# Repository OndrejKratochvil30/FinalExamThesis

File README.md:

# FinalExamThesis
FinalExamThesis

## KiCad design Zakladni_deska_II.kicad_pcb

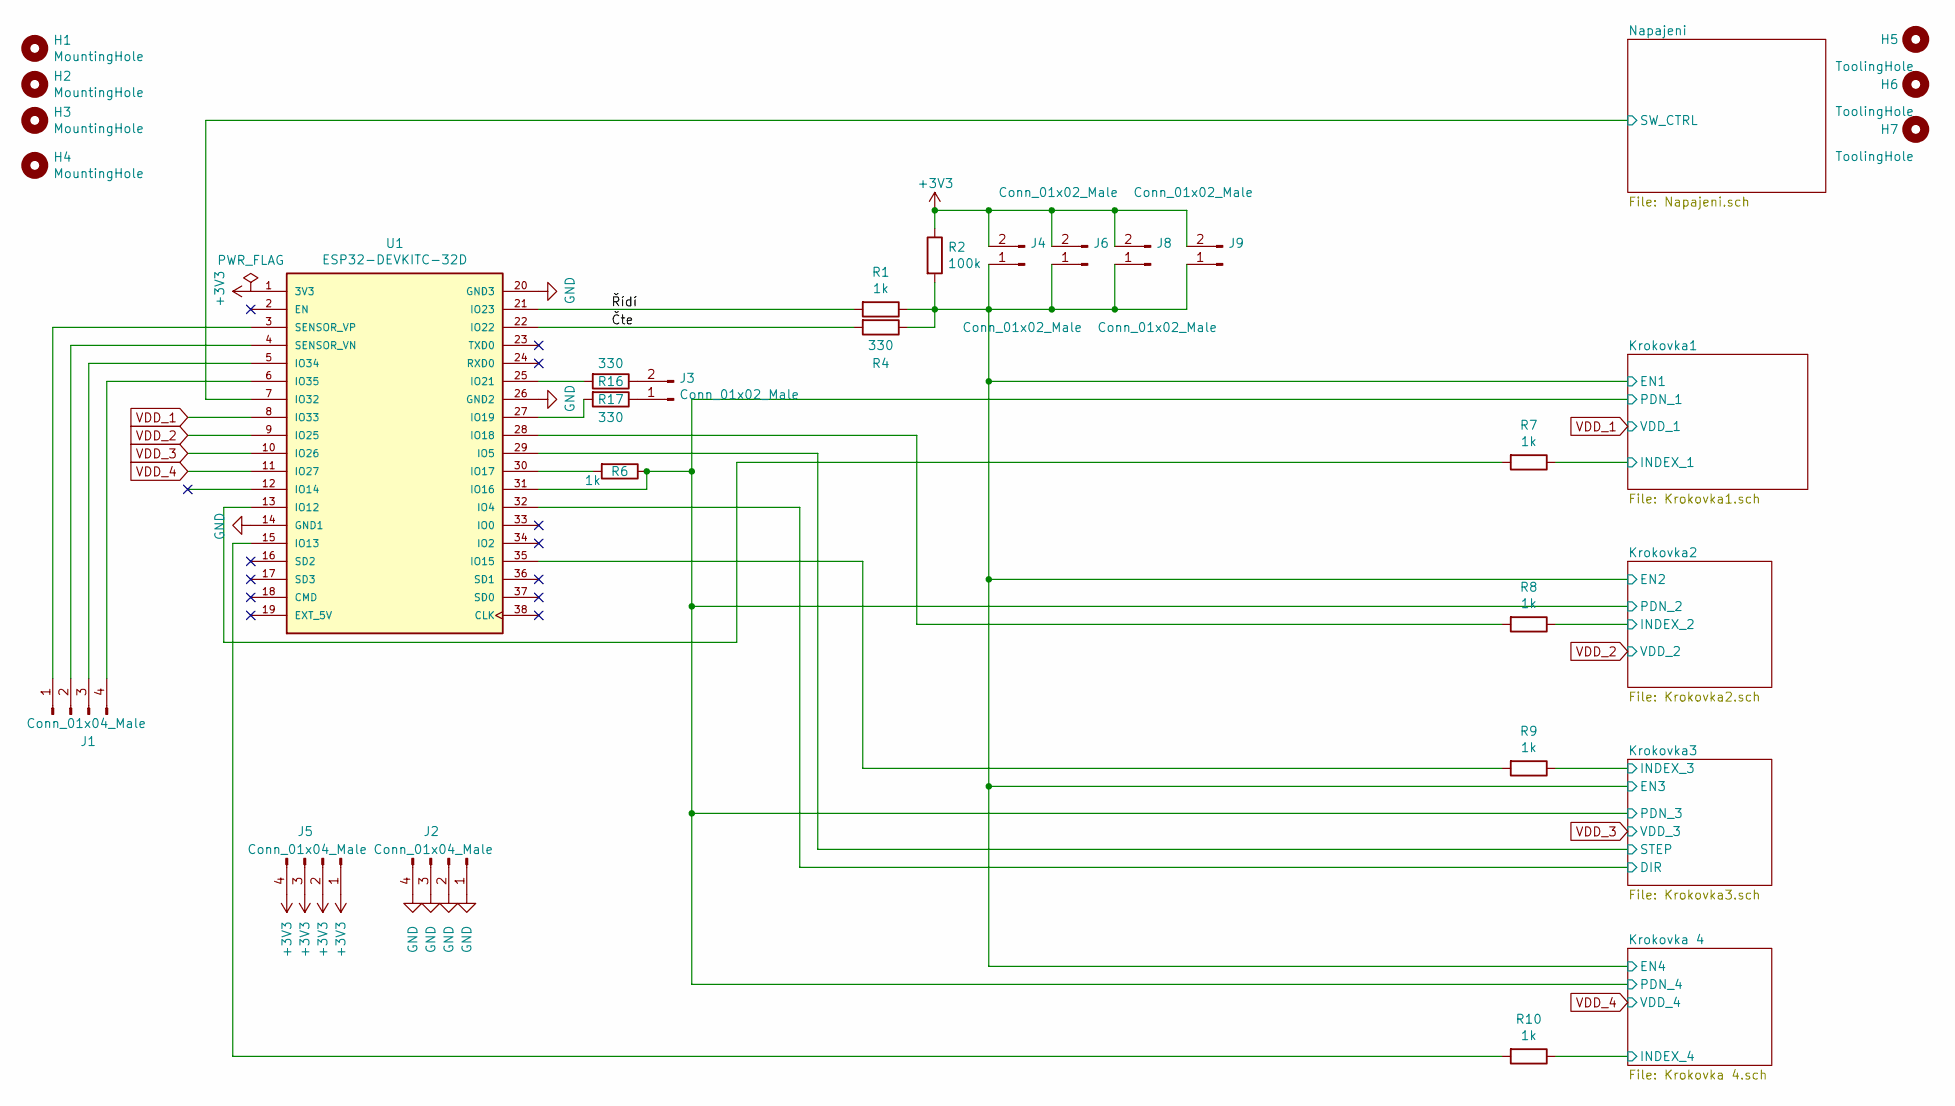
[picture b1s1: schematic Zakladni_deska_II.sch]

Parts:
H1, H2, H3, H4: MountingHole; MountingHole_2mm; JLCPCB_IGNORE 1
H5, H6, H7: ToolingHole; Tooling_Hole_2; JLCPCB_IGNORE 1
J1, J2, J5: Conn_01x04_Male; PinHeader_1x04_P2.54mm_Vertical; JLCPCB_IGNORE 1
J3, J4, J6, J8, J9: Conn_01x02_Male; PinHeader_1x02_P2.54mm_Vertical; JLCPCB_IGNORE 1
R1, R6, R7, R8, R9, R10: 1k; R_0805_2012Metric_Pad1.20x1.40mm_HandSolder; LCSC C17379
R2: 100k; R_0805_2012Metric_Pad1.20x1.40mm_HandSolder; LCSC C17422
R4, R16, R17: 330; R_0805_2012Metric_Pad1.20x1.40mm_HandSolder; LCSC C17617
U1: ESP32-DEVKITC-32D; MODULE_ESP32-DEVKITC-32D; PARTREV 4; JLCPCB_IGNORE 1

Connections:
+3V3: J4.2, J5.1, J5.2, J5.3, J5.4, J6.2, J8.2, J9.2, R2.1, U1.1 (3V3); also elsewhere on the board
/Krokovka1/EN1: J4.1, J6.1, J8.1, J9.1, R1.1, R2.2, R4.1; also elsewhere on the board
/Krokovka1/INDEX_1: R7.1; also elsewhere on the board
/Krokovka1/PDN_1: R6.1, U1.31 (IO16); also elsewhere on the board
/Krokovka2/INDEX_2: R8.1; also elsewhere on the board
/Krokovka3/DIR: U1.32 (IO4); also elsewhere on the board
/Krokovka3/INDEX_3: R9.1; also elsewhere on the board
/Krokovka3/STEP: U1.29 (IO5); also elsewhere on the board
/Krokovka 4/INDEX_4: R10.1; also elsewhere on the board
/Napajeni/SW_CTRL: U1.7 (IO32); also elsewhere on the board
/Čte: R4.2, U1.22 (IO22)
/Řídí: R1.2, U1.21 (IO23)
GND: J2.1, J2.2, J2.3, J2.4, U1.14 (GND1), U1.20 (GND3), U1.26 (GND2); also elsewhere on the board
unnamed: J1.1, U1.3 (SENSOR_VP)
unnamed: J1.2, U1.4 (SENSOR_VN)
unnamed: J1.3, U1.5 (IO34)
unnamed: J1.4, U1.6 (IO35)
unnamed: J3.1, R17.1
unnamed: J3.2, R16.1
unnamed: R6.2, U1.30 (IO17)
unnamed: R7.2, U1.13 (IO12)
unnamed: R8.2, U1.28 (IO18)
unnamed: R9.2, U1.35 (IO15)
unnamed: R10.2, U1.15 (IO13)
unnamed: R16.2, U1.25 (IO21)
unnamed: R17.2, U1.27 (IO19)
VDD_1: U1.8 (IO33); also elsewhere on the board
VDD_2: U1.9 (IO25); also elsewhere on the board
VDD_3: U1.10 (IO26); also elsewhere on the board
VDD_4: U1.11 (IO27); also elsewhere on the board

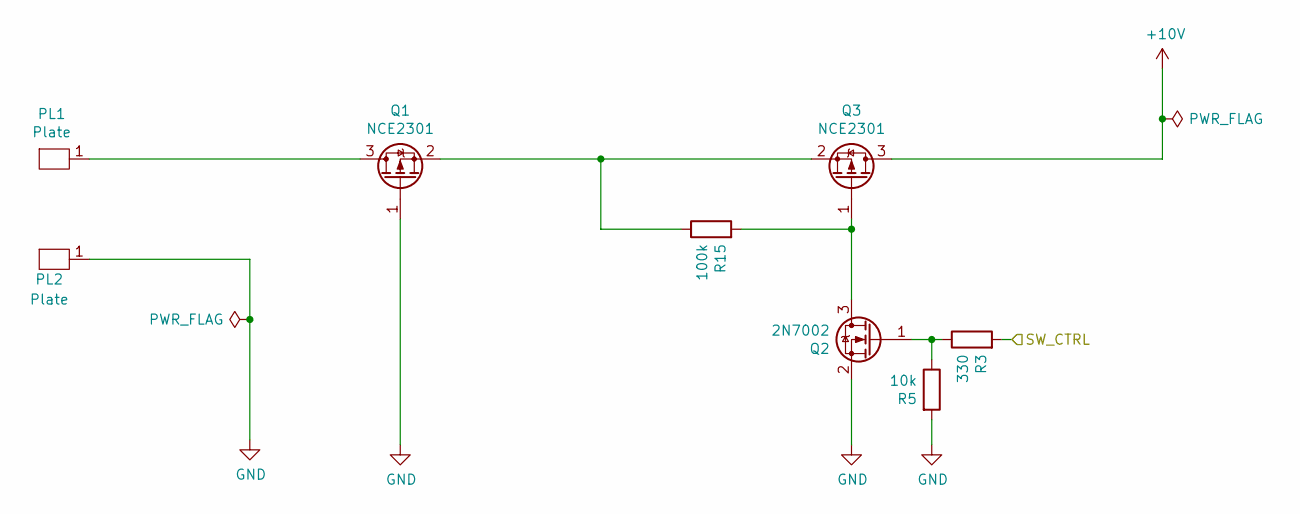
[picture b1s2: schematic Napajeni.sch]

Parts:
PL1, PL2: Plate; JLCPCB_IGNORE 1
Q1, Q3: NCE2301; SOT-23; LCSC C113201
Q2: 2N7002; SOT-23; LCSC C8545
R3: 330; R_0805_2012Metric_Pad1.20x1.40mm_HandSolder; LCSC C17617
R5: 10k; R_0805_2012Metric_Pad1.20x1.40mm_HandSolder; LCSC C17429
R15: 100k; R_0805_2012Metric_Pad1.20x1.40mm_HandSolder; LCSC C17422

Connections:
+10V: Q3.3 (D); also elsewhere on the board
/Napajeni/SW_CTRL: R3.2; also elsewhere on the board
GND: PL2.1, Q1.1 (G), Q2.2 (S), R5.2; also elsewhere on the board
unnamed: PL1.1, Q1.3 (D)
unnamed: Q1.2 (S), Q3.2 (S), R15.1
unnamed: Q2.1 (G), R3.1, R5.1
unnamed: Q2.3 (D), Q3.1 (G), R15.2

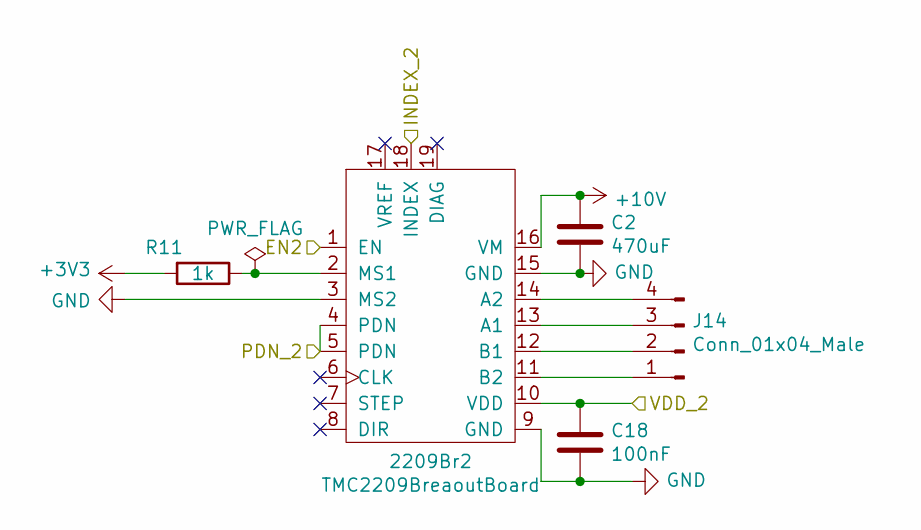
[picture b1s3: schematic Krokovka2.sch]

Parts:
2209Br2: TMC2209BreaoutBoard; TMC_2209_Breaout_Board; JLCPCB_IGNORE 1
C2: 470uF; CP_Radial_D10.0mm_P2.50mm; LCSC C34642
C18: 100nF; C_0402_1005Metric_Pad0.74x0.62mm_HandSolder; LCSC C1525
J14: Conn_01x04_Male; PinHeader_1x04_P2.54mm_Vertical; JLCPCB_IGNORE 1
R11: 1k; R_0805_2012Metric_Pad1.20x1.40mm_HandSolder; LCSC C17379

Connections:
+3V3: R11.2; also elsewhere on the board
+10V: 2209Br2.16 (VM), C2.1; also elsewhere on the board
/Krokovka1/EN1: 2209Br2.1 (EN); also elsewhere on the board
/Krokovka1/PDN_1: 2209Br2.4 (PDN), 2209Br2.5 (PDN); also elsewhere on the board
/Krokovka2/INDEX_2: 2209Br2.18 (INDEX); also elsewhere on the board
GND: 2209Br2.3 (MS2), 2209Br2.9 (GND), 2209Br2.15 (GND), C2.2, C18.2; also elsewhere on the board
unnamed: 2209Br2.2 (MS1), R11.1
unnamed: 2209Br2.11 (B2), J14.1
unnamed: 2209Br2.12 (B1), J14.2
unnamed: 2209Br2.13 (A1), J14.3
unnamed: 2209Br2.14 (A2), J14.4
VDD_2: 2209Br2.10 (VDD), C18.1; also elsewhere on the board

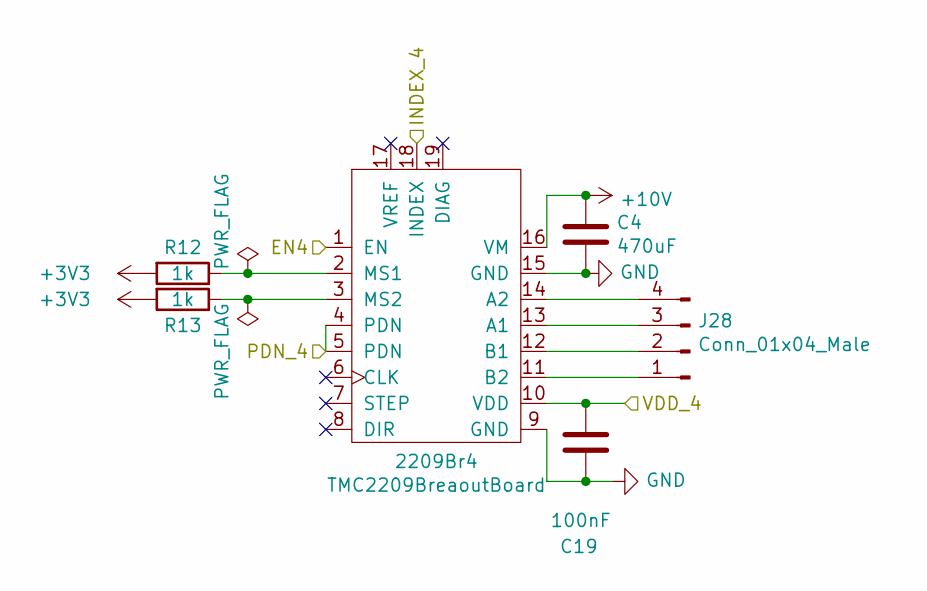
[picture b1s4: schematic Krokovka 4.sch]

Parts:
2209Br4: TMC2209BreaoutBoard; TMC_2209_Breaout_Board; JLCPCB_IGNORE 1
C4: 470uF; CP_Radial_D10.0mm_P2.50mm; LCSC C34642
C19: 100nF; C_0402_1005Metric_Pad0.74x0.62mm_HandSolder; LCSC C1525
J28: Conn_01x04_Male; PinHeader_1x04_P2.54mm_Vertical; JLCPCB_IGNORE 1
R12, R13: 1k; R_0805_2012Metric_Pad1.20x1.40mm_HandSolder; LCSC C17379

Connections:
+3V3: R12.2, R13.2; also elsewhere on the board
+10V: 2209Br4.16 (VM), C4.1; also elsewhere on the board
/Krokovka1/EN1: 2209Br4.1 (EN); also elsewhere on the board
/Krokovka1/PDN_1: 2209Br4.4 (PDN), 2209Br4.5 (PDN); also elsewhere on the board
/Krokovka 4/INDEX_4: 2209Br4.18 (INDEX); also elsewhere on the board
GND: 2209Br4.9 (GND), 2209Br4.15 (GND), C4.2, C19.1; also elsewhere on the board
unnamed: 2209Br4.2 (MS1), R12.1
unnamed: 2209Br4.3 (MS2), R13.1
unnamed: 2209Br4.11 (B2), J28.1
unnamed: 2209Br4.12 (B1), J28.2
unnamed: 2209Br4.13 (A1), J28.3
unnamed: 2209Br4.14 (A2), J28.4
VDD_4: 2209Br4.10 (VDD), C19.2; also elsewhere on the board

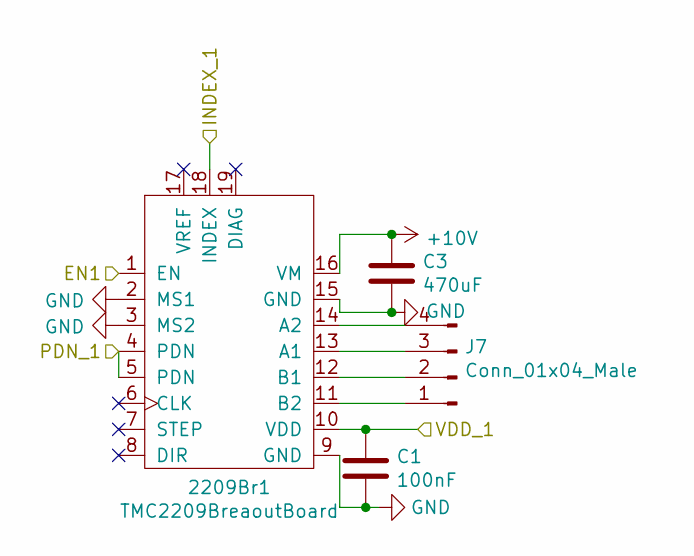
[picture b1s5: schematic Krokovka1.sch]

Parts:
2209Br1: TMC2209BreaoutBoard; TMC_2209_Breaout_Board; JLCPCB_IGNORE 1
C1: 100nF; C_0402_1005Metric_Pad0.74x0.62mm_HandSolder; LCSC C1525
C3: 470uF; CP_Radial_D10.0mm_P2.50mm; LCSC C34642
J7: Conn_01x04_Male; PinHeader_1x04_P2.54mm_Vertical; JLCPCB_IGNORE 1

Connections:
+10V: 2209Br1.16 (VM), C3.1; also elsewhere on the board
/Krokovka1/EN1: 2209Br1.1 (EN); also elsewhere on the board
/Krokovka1/INDEX_1: 2209Br1.18 (INDEX); also elsewhere on the board
/Krokovka1/PDN_1: 2209Br1.4 (PDN), 2209Br1.5 (PDN); also elsewhere on the board
GND: 2209Br1.2 (MS1), 2209Br1.3 (MS2), 2209Br1.9 (GND), 2209Br1.15 (GND), C1.2, C3.2; also elsewhere on the board
unnamed: 2209Br1.11 (B2), J7.1
unnamed: 2209Br1.12 (B1), J7.2
unnamed: 2209Br1.13 (A1), J7.3
unnamed: 2209Br1.14 (A2), J7.4
VDD_1: 2209Br1.10 (VDD), C1.1; also elsewhere on the board

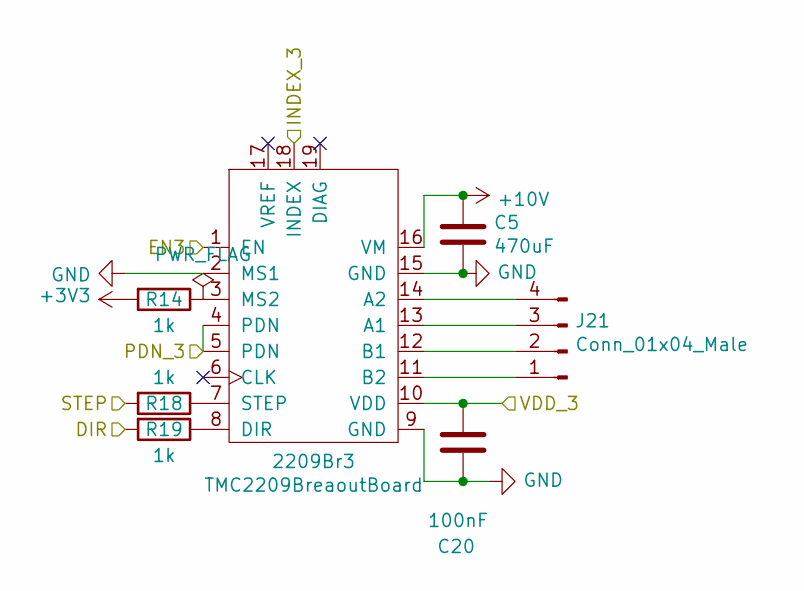
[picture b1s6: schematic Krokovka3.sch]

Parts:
2209Br3: TMC2209BreaoutBoard; TMC_2209_Breaout_Board; JLCPCB_IGNORE 1
C5: 470uF; CP_Radial_D10.0mm_P2.50mm; LCSC C34642
C20: 100nF; C_0402_1005Metric_Pad0.74x0.62mm_HandSolder; LCSC C1525
J21: Conn_01x04_Male; PinHeader_1x04_P2.54mm_Vertical; JLCPCB_IGNORE 1
R14, R18, R19: 1k; R_0805_2012Metric_Pad1.20x1.40mm_HandSolder; LCSC C17379

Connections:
+3V3: R14.2; also elsewhere on the board
+10V: 2209Br3.16 (VM), C5.1; also elsewhere on the board
/Krokovka1/EN1: 2209Br3.1 (EN); also elsewhere on the board
/Krokovka1/PDN_1: 2209Br3.4 (PDN), 2209Br3.5 (PDN); also elsewhere on the board
/Krokovka3/DIR: R19.2; also elsewhere on the board
/Krokovka3/INDEX_3: 2209Br3.18 (INDEX); also elsewhere on the board
/Krokovka3/STEP: R18.2; also elsewhere on the board
GND: 2209Br3.2 (MS1), 2209Br3.9 (GND), 2209Br3.15 (GND), C5.2, C20.1; also elsewhere on the board
unnamed: 2209Br3.3 (MS2), R14.1
unnamed: 2209Br3.7 (STEP), R18.1
unnamed: 2209Br3.8 (DIR), R19.1
unnamed: 2209Br3.11 (B2), J21.1
unnamed: 2209Br3.12 (B1), J21.2
unnamed: 2209Br3.13 (A1), J21.3
unnamed: 2209Br3.14 (A2), J21.4
VDD_3: 2209Br3.10 (VDD), C20.2; also elsewhere on the board

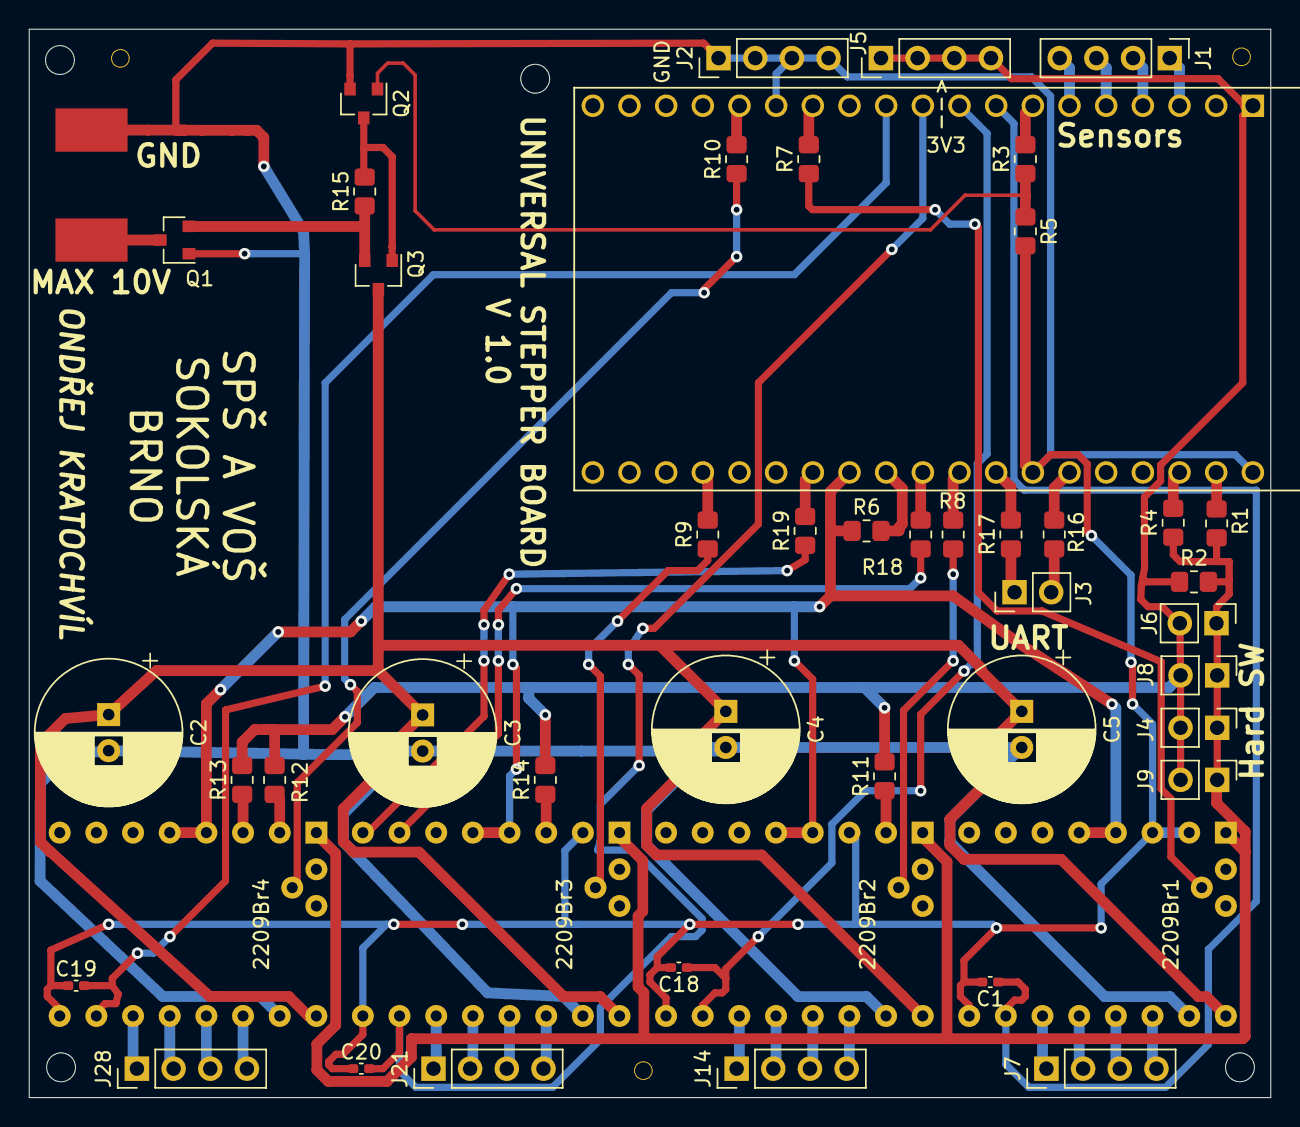
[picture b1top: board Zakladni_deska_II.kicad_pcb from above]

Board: 2 copper layers, 86.0 x 74.0 mm, 56 parts (0 on the bottom side), 57 nets.

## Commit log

2020-11-05 inicializuje repozitare
2021-02-02 Verze 0.1, 4. rocnik
2021-02-02 Verze 0.2, Indexy
2021-02-03 Deska 0.5
2021-02-03 Oprava 0.5
2021-02-04 DIR STEP ven
2021-02-04 Doplnen reset
2021-02-04 Mosfet
2021-02-04 Jirka upravy
2021-02-08 Hotové schéma
2021-02-08 Drobná úprava
2021-02-10 Hotová deska
2021-02-14 Deska + porty
2021-02-14 Deska2
2021-02-15 Zmenseni desky
2021-02-15 Jirka
2021-02-16 Nová Deska
2021-02-16 Deska 1.1
2021-02-17 release candidate
2021-02-18 Ordered
